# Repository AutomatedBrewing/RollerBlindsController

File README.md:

# Embedded build system
Sample implementation

## Setup

Before building, install all required dependencies:

```bash
./setup_repo.sh
```

For detailed information about dependencies, see [DEPENDENCIES.md](DEPENDENCIES.md).

## Building
To build specific target:
`./build.sh -c blink_F072`

## Formatting & Linting

The project uses `clang-format` and `clang-tidy` for code quality.

You can:
1. Format whole codebase: `./format_all.sh`
2. Run linting: `./lint_all.sh`
3. Check formatting on commit: `git-clang-format --diff --style=file HEAD`

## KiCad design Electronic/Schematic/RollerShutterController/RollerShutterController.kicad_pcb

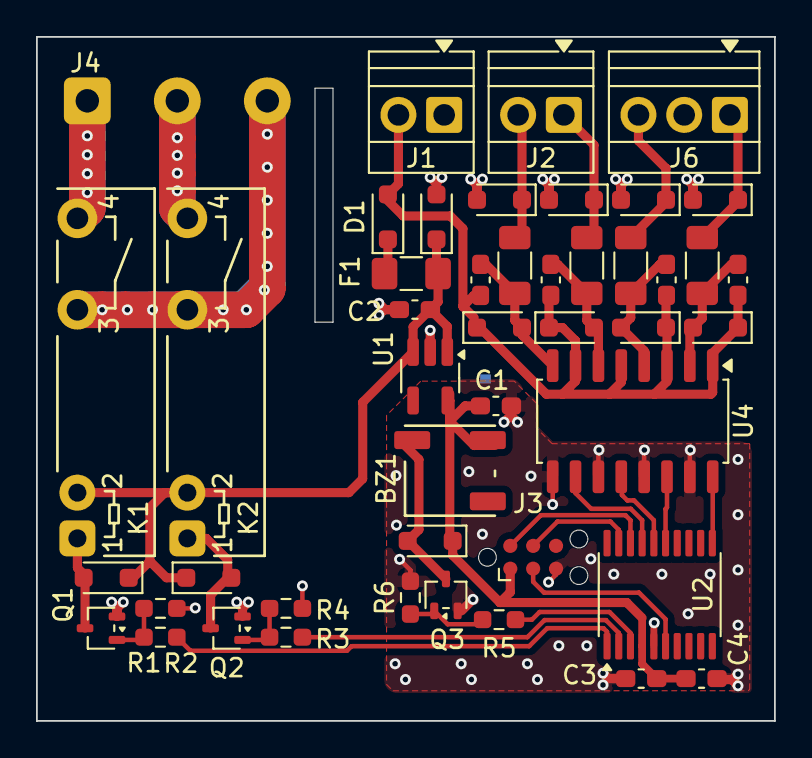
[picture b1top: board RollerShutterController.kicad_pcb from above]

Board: 2 copper layers, 41.0 x 38.0 mm, 47 parts (1 on the bottom side), 33 nets.

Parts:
BZ1: Buzzer; LD-BZEL-T56-0505
C1, C2, C4: 1u 25V; C_0603_1608Metric_Pad1.08x0.95mm_HandSolder
C3, C5, C6, C7, C8: 100n 50V; C_0603_1608Metric_Pad1.08x0.95mm_HandSolder
D1: SDB160WS-AQ; D_SOD-323_HandSoldering
D2, D6, D7, D8, D9: STS321150U751; D_SOD-323_HandSoldering
D3, D4, D5, D12, D13, D14, D15: 1N4148WSTR; D_SOD-323_HandSoldering
F1: SN005-60; Fuse_1206_3216Metric_Pad1.42x1.75mm_HandSolder
J1, J2: Conn_01x02_Socket; TerminalBlock_Xinya_XY308-2.54-2P_1x02_P2.54mm_Horizontal
J3: TC2030; Tag-Connect_TC2030-IDC-NL_2x03_P1.27mm_Vertical
J4: Conn_01x03_Socket; DG301-5.0
J6: Conn_01x03_Socket; TerminalBlock_Xinya_XY308-2.54-3P_1x03_P2.54mm_Horizontal
JP1: SolderJumper_2_Bridged; SolderJumper-2_P1.3mm_Bridged_Pad1.0x1.5mm
K1, K2: AZ921-1A-12DE; AZ921
Q1, Q2, Q3: BSS138; SOT-323_SC-70
R1, R4, R6: 100k; R_0603_1608Metric_Pad0.98x0.95mm_HandSolder
R2, R3, R5: 330R; R_0603_1608Metric_Pad0.98x0.95mm_HandSolder
R8, R9, R11, R13: 1K; R_1206_3216Metric_Pad1.30x1.75mm_HandSolder
U1: LDK320M33R; SOT-23-5_HandSoldering
U2: STM32C011F4Px; TSSOP-20_4.4x6.5mm_P0.65mm
U4: LTV-247; SOP-16_4.4x10.4mm_P1.27mm

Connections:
230V_AC: J4.3, K1.13, K2.13
+3V3: BZ1.1 (+), C1.1, C3.1, C4.1, D5.1 (K), J3.1, U1.5 (OUT), U2.4 (VDD)
+12V: C5.1, C6.1, C7.1, C8.1, D1.2 (A), D12.1 (K), D13.1 (K), D14.1 (K), D15.1 (K), J1.2, U4.1, U4.3, U4.5, U4.7
+12V_SAFE: C2.1, D2.1 (K), D3.1 (K), D4.1 (K), F1.2, K1.A2, K2.A2, U1.1 (IN), U1.3 (EN)
BUTTON_LOCAL_DOWN: U2.11 (PA4), U4.16
BUTTON_LOCAL_DOWN_EXT: D9.1 (K), J6.1, R13.1
BUTTON_LOCAL_UP: U2.15 (PA8), U4.14
BUTTON_LOCAL_UP_EXT: D8.1 (K), J6.3, R11.1
BUTTON_REMOTE_DOWN: U2.16 (PA9/PA11), U4.12
BUTTON_REMOTE_DOWN_EXT: D7.1 (K), J2.1, R9.1
BUTTON_REMOTE_UP: U2.17 (PA10/PA12), U4.10
BUTTON_REMOTE_UP_EXT: D6.1 (K), J2.2, R8.1
BUZZER: R5.1, U2.3 (PC15)
GND: C1.2, C3.2, C4.2, J3.5, JP1.2 (B), Q3.2 (S), R6.2, U2.5 (VSS), U4.9, U4.11, U4.13, U4.15
GNDPWR: C2.2, D2.2 (A), D6.2 (A), D7.2 (A), D8.2 (A), D9.2 (A), J1.1, J6.2, JP1.1 (A), Q1.2 (S), Q2.2 (S), R1.2, R4.2, U1.2 (GND)
MOTOR_DOWN: J4.2, K2.14
MOTOR_UP: J4.1, K1.14
NRST: J3.3, U2.6 (PF2)
unnamed: BZ1.2 (-), D5.2 (A), Q3.3 (D)
unnamed: D1.1 (K), F1.1
unnamed: D3.2 (A), K1.A1, Q1.3 (D)
unnamed: D4.2 (A), K2.A1, Q2.3 (D)
unnamed: C5.2, D12.2 (A), R8.2, U4.8
unnamed: C6.2, D13.2 (A), R9.2, U4.6
unnamed: C7.2, D14.2 (A), R11.2, U4.4
unnamed: C8.2, D15.2 (A), R13.2, U4.2
unnamed: Q1.1 (G), R1.1, R2.2
unnamed: Q2.1 (G), R3.2, R4.1
unnamed: Q3.1 (G), R5.2, R6.1
RELAY_DOWN: R3.1, U2.2 (PC14)
RELAY_UP: R2.1, U2.1 (PB7)
SWCLK: J3.4, U2.19 (PA14)
SWDIO: J3.2, U2.18 (PA13)

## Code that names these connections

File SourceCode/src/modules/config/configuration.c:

/*
 * configuration.c
 *
 *  Created on: 1 Oct 2022
 *      Author: Kamil Lazowski
 */

/* Private includes ----------------------------------------------------------*/
#include "configuration.h"
#include "button_pressed_event.h"
#include "button_released_event.h"

#include "flash.h"
#include "nvm.h"

#include "utils.h"

/* Private define ------------------------------------------------------------*/
#define MOTOR_SAFETY_TIMER_TIMEOUT (MINUTES(2))

#define BUTTON_TIMINGS_DEFAULT                                                                                         \
    {                                                                                                                  \
        .debounce_time = 20, .long_press_time = 200, .very_long_press_time = 5000                                      \
    }

#define BUTTON_EVENTS_DEFAULT                                                                                          \
    {                                                                                                                  \
        .event_pressed = BUTTON_PRESSED_EVENT_ID, .event_released = BUTTON_RELEASED_EVENT_ID,                          \
    }

// #define DEFAULT_TRAVEL_TIME MINUTES(1)
#define DEFAULT_TRAVEL_TIME (5000)
/* Private typedef -----------------------------------------------------------*/
/* Private macro -------------------------------------------------------------*/
/* Private variables ---------------------------------------------------------*/
/*-------------------   BUTTONS */
static const struct button_configuration button_local_up = {
    .pin_id = BUTTON_LOCAL_UP_PIN_ID,
    .timings = BUTTON_TIMINGS_DEFAULT,
    .events = BUTTON_EVENTS_DEFAULT,
};

static const struct button_configuration button_local_down = {
    .pin_id = BUTTON_LOCAL_DOWN_PIN_ID,
    .timings = BUTTON_TIMINGS_DEFAULT,
    .events = BUTTON_EVENTS_DEFAULT,
};

static const struct button_configuration button_remote_up = {
    .pin_id = BUTTON_REMOTE_UP_PIN_ID,
    .timings = BUTTON_TIMINGS_DEFAULT,
    .events = BUTTON_EVENTS_DEFAULT,
};

static const struct button_configuration button_remote_down = {
    .pin_id = BUTTON_REMOTE_DOWN_PIN_ID,
    .timings = BUTTON_TIMINGS_DEFAULT,
    .events = BUTTON_EVENTS_DEFAULT,
};

static const struct device_configuration button_devices_list[] = {
    {
        .id = DEVICE_BUTTON_LOCAL_UP,
        .type = DEVICE_TYPE_BUTTON,
        .config = &button_local_up,
    },

    {
        .id = DEVICE_BUTTON_LOCAL_DOWN,
        .type = DEVICE_TYPE_BUTTON,
        .config = &button_local_down,
    },

    {
        .id = DEVICE_BUTTON_REMOTE_UP,
        .type = DEVICE_TYPE_BUTTON,
        .config = &button_remote_up,
    },
    {
        .id = DEVICE_BUTTON_REMOTE_DOWN,
        .type = DEVICE_TYPE_BUTTON,
        .config = &button_remote_down,
    },
};

/*-------------------   MOTOR */
static const struct motor_configuration motor_config = {
    .motor_up_pin_id = MOTOR_UP_PIN_ID,
    .motor_down_pin_id = MOTOR_DOWN_PIN_ID,
    .timeout = MOTOR_SAFETY_TIMER_TIMEOUT,
};

static const struct device_configuration motor_devices_list[] = {
    {
        .id = DEVICE_MOTOR,
        .type = DEVICE_TYPE_MOTOR,
        .config = &motor_config,
    },
};

/*-------------------   BUZZER */
static const struct buzzer_configuration buzzer_config = {
    .pin_id = BUZZER_PIN_ID,
    .timings =
        {
            .on_time = 100,
            .off_time = 100,
            .repetitions = 2,
        },
};

static const struct device_configuration ui_devices_list[] = {
    {
        .id = DEVICE_BUZZER,
        .type = DEVICE_TYPE_BUZZER,
        .config = &buzzer_config,
    },
};

/*-------------------   NVM */
static const struct nvm_object nvm_objects[] = {
    {.id = NVM_ID_TRAVEL_TIME, .size = sizeof(struct travel_time)},
};

static const struct nvm_backend nvm_backend = {
    .size = 2048U, .erase_size = 256U,
    /*
        .read = flash_read,
        .write = flash_program,
        .erase = flash_erase
        */
};

static const struct nvm_configuration nvm_config = {
    .configuration = {.backend = &nvm_backend,
                      .objects = nvm_objects,
                      .object_count = sizeof(nvm_objects) / sizeof(nvm_objects[0])},
    .default_time = DEFAULT_TRAVEL_TIME,
};

static const struct device_configuration nvm_devices_list[] = {
    {
        .id = DEVICE_NVM,
        .type = DEVICE_TYPE_NVM,
        .config = &nvm_config,
    },
};
/* Private function prototypes -----------------------------------------------*/
/* Private function bodies ---------------------------------------------------*/

const struct device_configuration *get_list_of_devices_by_type(enum device_type type, uint8_t *devices_count)
{
    if (devices_count == NULL)
    {
        return NULL;
    }

    switch (type)
    {
    case DEVICE_TYPE_BUTTON:
        *devices_count = ARRAY_SIZE(button_devices_list);
        return button_devices_list;

    case DEVICE_TYPE_BUZZER:
        *devices_count = ARRAY_SIZE(ui_devices_list);
        return ui_devices_list;

    case DEVICE_TYPE_MOTOR:
        *devices_count = ARRAY_SIZE(motor_devices_list);
        return motor_devices_list;

    case DEVICE_TYPE_NVM:
        *devices_count = ARRAY_SIZE(nvm_devices_list);
        return nvm_devices_list;

    default:
        *devices_count = 0;
        return NULL;
    }
}

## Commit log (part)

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2026-06-15 Modelled requirements and constraints.
2026-06-15 Aligning the project to SysMod in progress.
2026-06-16 Corrected requirements and constraints.
2026-06-16 Corrected miscellaneous items.
2026-06-16 Started work on identification of system processes.
2026-06-18 Added Use Case Activities, but haven't linked them.
2026-06-19 Added tracebility from use cases to use case activities.
2026-06-19 Added skeletons for verification.
2026-06-19 Added initial sketch of functional architecture
2026-06-23 Corrected use-case activities and started work on functional architecture.
2026-06-23 Added functional architecture.
2026-06-24 Refactored use-cases and use case activities. Tracebilty not fixed.
2026-06-24 Fixed tracebility.
